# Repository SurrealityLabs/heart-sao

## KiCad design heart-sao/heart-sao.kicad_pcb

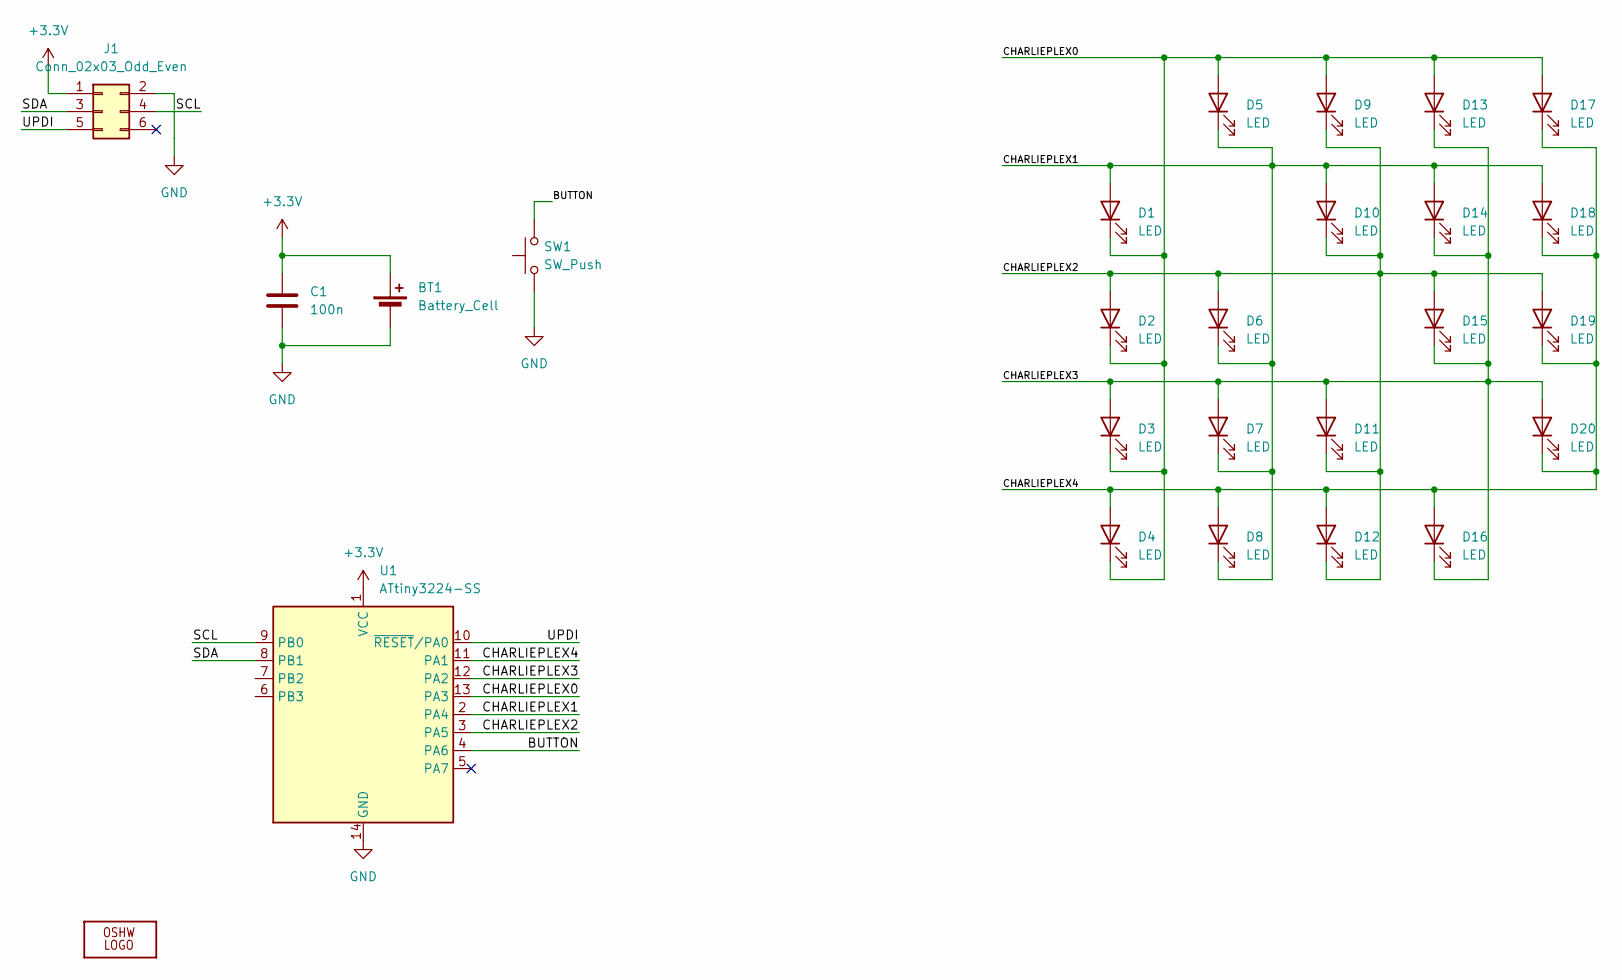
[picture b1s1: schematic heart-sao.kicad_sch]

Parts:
BT1: Battery_Cell; BatteryHolder_Keystone_3000_1x12mm
C1: 100n; C_1206_3216Metric
D1, D2, D3, D4, D5, D6, D7, D8, D9, D10, D11, D12, D13, D14, D15, D16, D17, D18, D19, D20: LED; LED_1206_3216Metric
J1: Conn_02x03_Odd_Even; IDC-Header_2x03_P2.54mm_Vertical_SMD
LOGO1: OSHW_LOGO_FILLX0100-NT; OSHW_FILLX100_NOTEXT
SW1: SW_Push; SW_SPST_CK_RS282G05A3
U1: ATtiny3224-SS; SOIC-14_3.9x8.7mm_P1.27mm

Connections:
+3.3V: BT1.1 (+), C1.1, J1.1, U1.1 (VCC)
/BUTTON: SW1.2, U1.4 (PA6)
/CHARLIEPLEX0: D1.1 (K), D2.1 (K), D3.1 (K), D4.1 (K), D5.2 (A), D9.2 (A), D13.2 (A), D17.2 (A), U1.13 (PA3)
/CHARLIEPLEX1: D1.2 (A), D5.1 (K), D6.1 (K), D7.1 (K), D8.1 (K), D10.2 (A), D14.2 (A), D18.2 (A), U1.2 (PA4)
/CHARLIEPLEX2: D2.2 (A), D6.2 (A), D9.1 (K), D10.1 (K), D11.1 (K), D12.1 (K), D15.2 (A), D19.2 (A), U1.3 (PA5)
/CHARLIEPLEX3: D3.2 (A), D7.2 (A), D11.2 (A), D13.1 (K), D14.1 (K), D15.1 (K), D16.1 (K), D20.2 (A), U1.12 (PA2)
/CHARLIEPLEX4: D4.2 (A), D8.2 (A), D12.2 (A), D16.2 (A), D17.1 (K), D18.1 (K), D19.1 (K), D20.1 (K), U1.11 (PA1)
/SCL: J1.4, U1.9 (PB0)
/SDA: J1.3, U1.8 (PB1)
/UPDI: J1.5, U1.10 (~RESET/PA0)
GND: BT1.2 (-), C1.2, J1.2, SW1.1, U1.14 (GND)

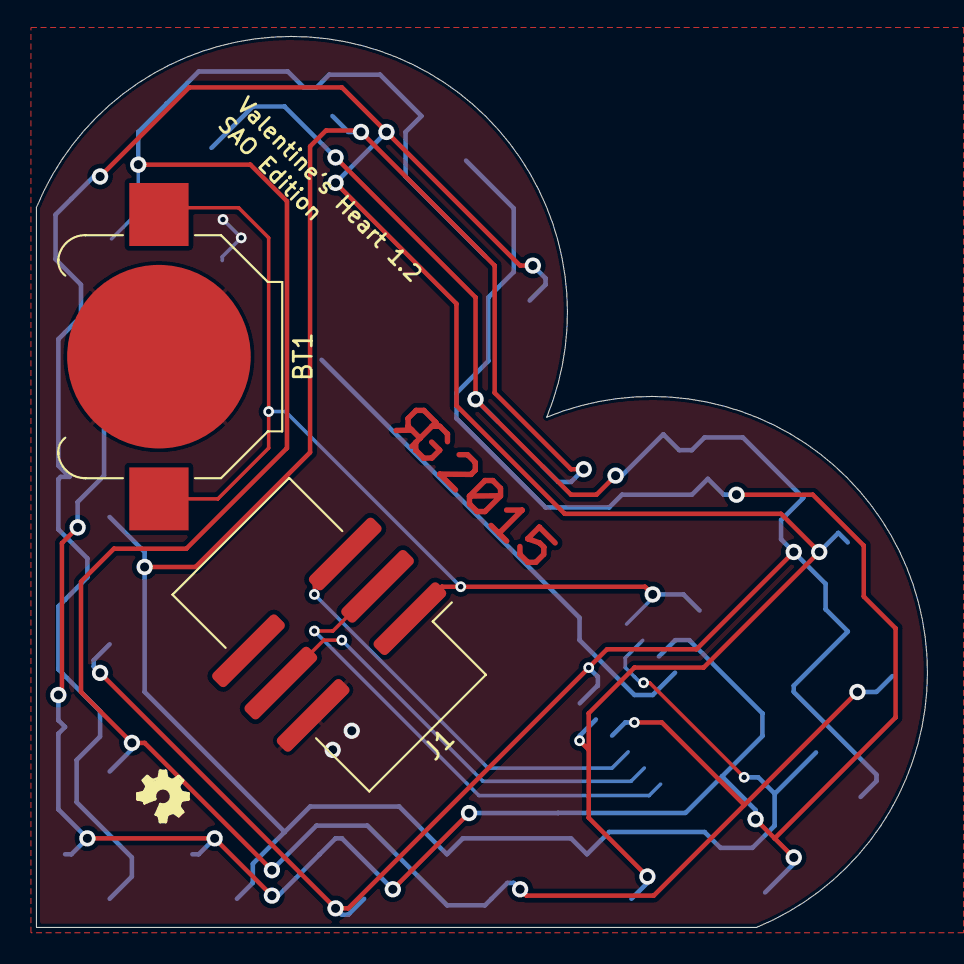
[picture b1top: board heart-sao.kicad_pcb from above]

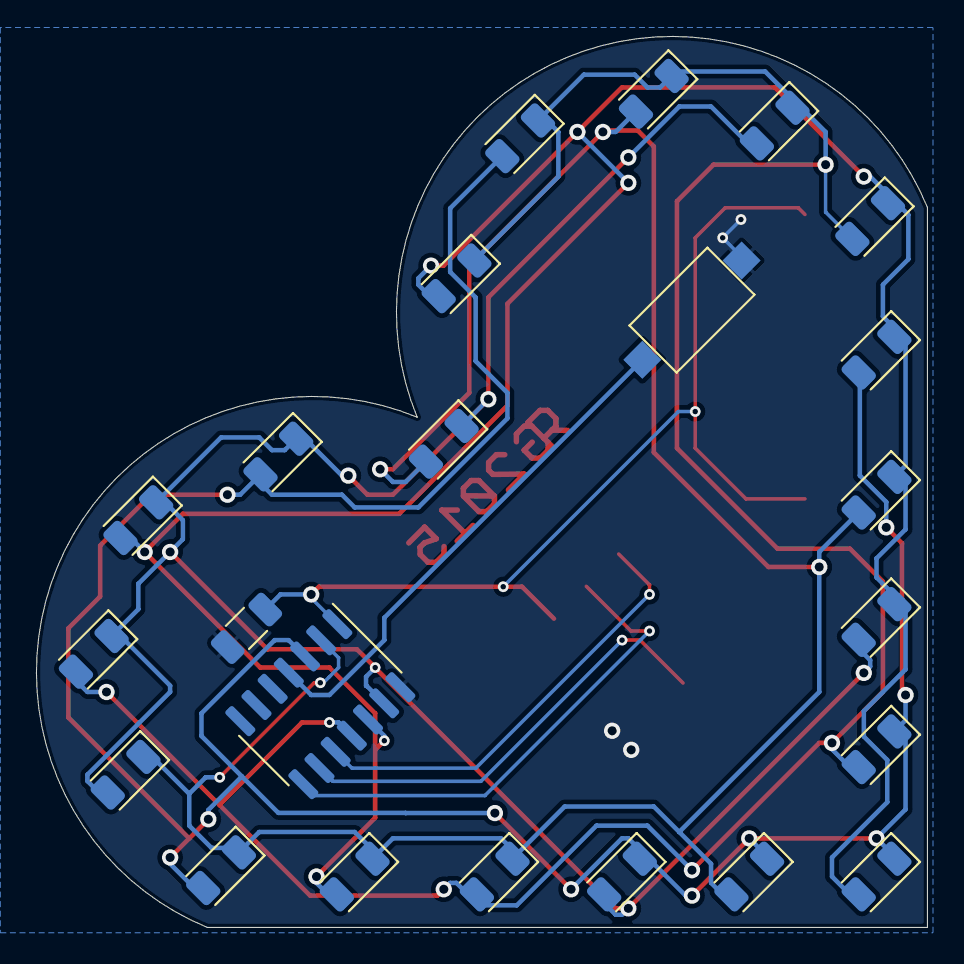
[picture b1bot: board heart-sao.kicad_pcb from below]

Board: 2 copper layers, 49.5 x 49.5 mm, 27 parts (23 on the bottom side), 11 nets.

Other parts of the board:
U$1: RGLOGO_SMALL_2015

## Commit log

2024-08-30 Adding PCB files
2024-08-31 Adding first stab at firmware, guaranteed that sleep mode doesn't work
